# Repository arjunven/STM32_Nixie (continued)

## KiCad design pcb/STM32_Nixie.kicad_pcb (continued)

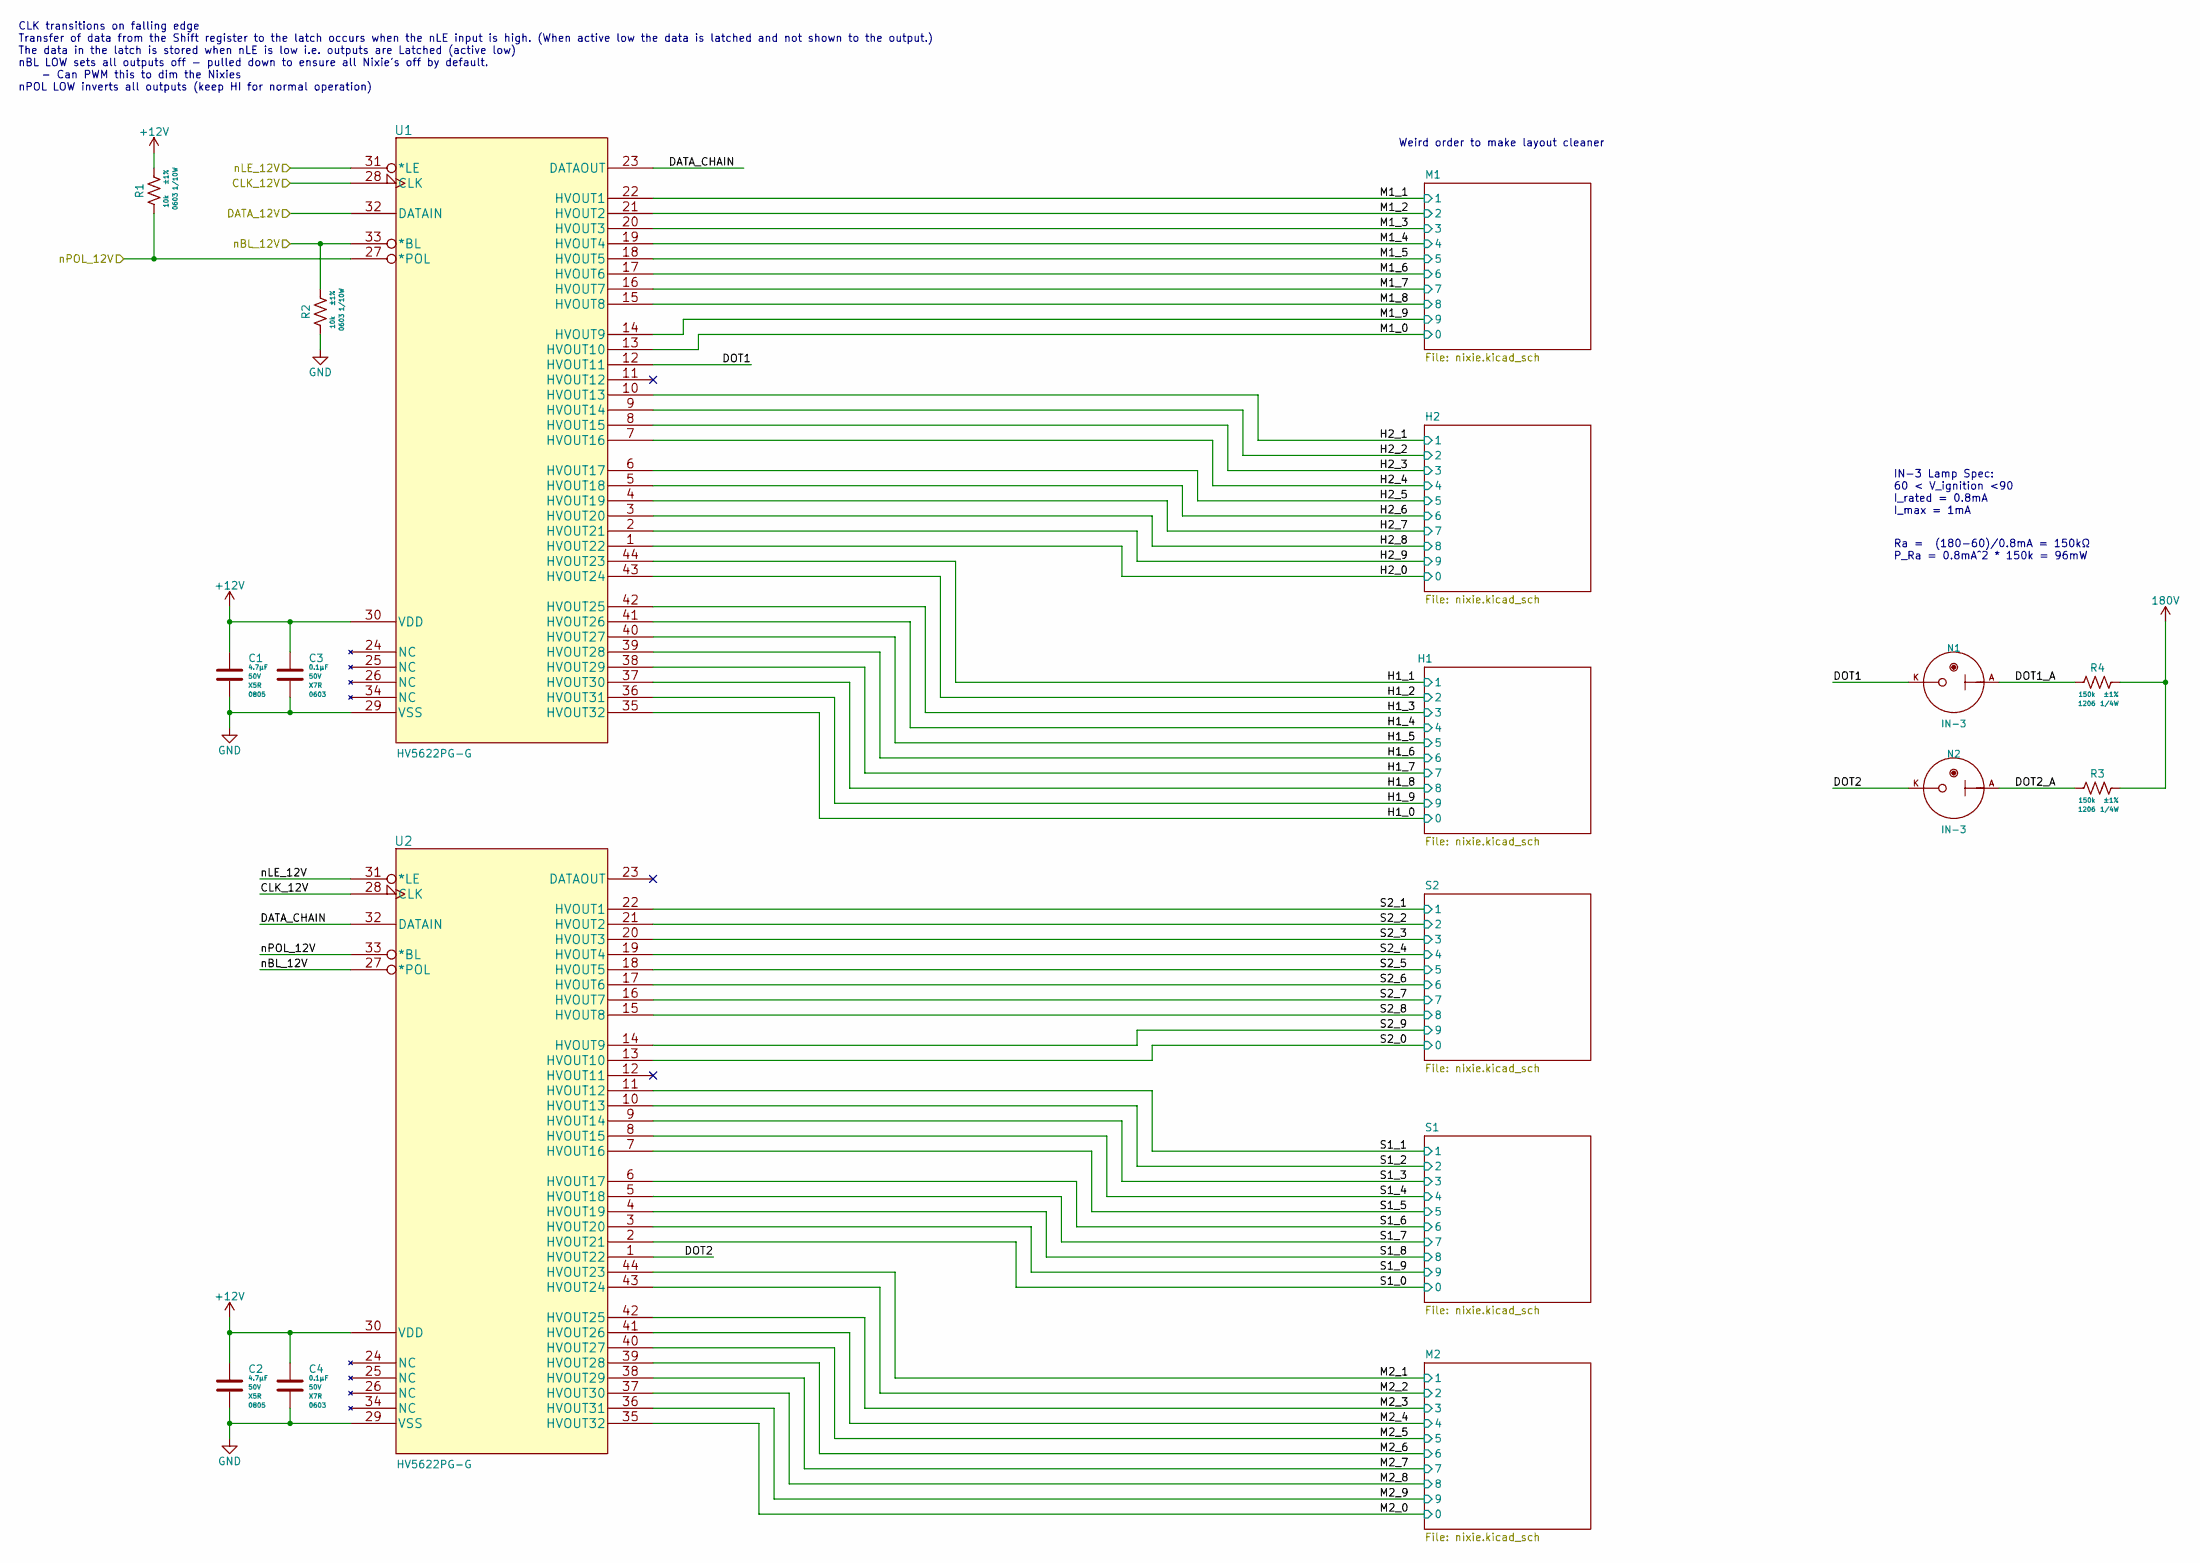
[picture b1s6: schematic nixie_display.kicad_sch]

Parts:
C1, C2: CAP_CER_4u7_50V_X5R_0805; C_0805_2012Metric; Voltage 50V; ManufacturerPN GRM21BR61H475KE51L
C3, C4: CAP_CER_0u1_50V_X7R_0603; C_0603_1608Metric; Voltage 50V; ManufacturerPN CL10B104KB8NNNC
N1, N2: IN-3
R1, R2: RES_10K_1P_1/10W_0603; R_0603_1608Metric; Tolerance ±1%; ManufacturerPN RC0603FR-0710KL
R3, R4: RES_150K_1P_1/4W_1206; R_1206_3216Metric; Tolerance ±1%; ManufacturerPN RC1206FR-07150KL
U1, U2: IC_SR_MC_HV5622PG-G; HV5622PG-G; ManufacturerPN HV5622PG-G

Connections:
180V: R3.1, R4.1; also elsewhere on the board
+12V: C1.1, C2.1, C3.1, C4.1, R1.1, U1.30 (VDD), U2.30 (VDD); also elsewhere on the board
/Nixie Display/DATA_CHAIN: U1.23 (DATAOUT), U2.32 (DATAIN)
/Nixie Display/DOT1: N1.K, U1.12 (HVOUT11)
/Nixie Display/DOT1_A: N1.A, R4.2
/Nixie Display/DOT2: N2.K, U2.1 (HVOUT22)
/Nixie Display/DOT2_A: N2.A, R3.2
/Nixie Display/H1_0: U1.35 (HVOUT32); also elsewhere on the board
/Nixie Display/H1_1: U1.44 (HVOUT23); also elsewhere on the board
/Nixie Display/H1_2: U1.43 (HVOUT24); also elsewhere on the board
/Nixie Display/H1_3: U1.42 (HVOUT25); also elsewhere on the board
/Nixie Display/H1_4: U1.41 (HVOUT26); also elsewhere on the board
/Nixie Display/H1_5: U1.40 (HVOUT27); also elsewhere on the board
/Nixie Display/H1_6: U1.39 (HVOUT28); also elsewhere on the board
/Nixie Display/H1_7: U1.38 (HVOUT29); also elsewhere on the board
/Nixie Display/H1_8: U1.37 (HVOUT30); also elsewhere on the board
/Nixie Display/H1_9: U1.36 (HVOUT31); also elsewhere on the board
/Nixie Display/H2_0: U1.1 (HVOUT22); also elsewhere on the board
/Nixie Display/H2_1: U1.10 (HVOUT13); also elsewhere on the board
/Nixie Display/H2_2: U1.9 (HVOUT14); also elsewhere on the board
/Nixie Display/H2_3: U1.8 (HVOUT15); also elsewhere on the board
/Nixie Display/H2_4: U1.7 (HVOUT16); also elsewhere on the board
/Nixie Display/H2_5: U1.6 (HVOUT17); also elsewhere on the board
/Nixie Display/H2_6: U1.5 (HVOUT18); also elsewhere on the board
/Nixie Display/H2_7: U1.4 (HVOUT19); also elsewhere on the board
/Nixie Display/H2_8: U1.3 (HVOUT20); also elsewhere on the board
/Nixie Display/H2_9: U1.2 (HVOUT21); also elsewhere on the board
/Nixie Display/M1_0: U1.13 (HVOUT10); also elsewhere on the board
/Nixie Display/M1_1: U1.22 (HVOUT1); also elsewhere on the board
/Nixie Display/M1_2: U1.21 (HVOUT2); also elsewhere on the board
/Nixie Display/M1_3: U1.20 (HVOUT3); also elsewhere on the board
/Nixie Display/M1_4: U1.19 (HVOUT4); also elsewhere on the board
/Nixie Display/M1_5: U1.18 (HVOUT5); also elsewhere on the board
/Nixie Display/M1_6: U1.17 (HVOUT6); also elsewhere on the board
/Nixie Display/M1_7: U1.16 (HVOUT7); also elsewhere on the board
/Nixie Display/M1_8: U1.15 (HVOUT8); also elsewhere on the board
/Nixie Display/M1_9: U1.14 (HVOUT9); also elsewhere on the board
/Nixie Display/M2_0: U2.35 (HVOUT32); also elsewhere on the board
/Nixie Display/M2_1: U2.44 (HVOUT23); also elsewhere on the board
/Nixie Display/M2_2: U2.43 (HVOUT24); also elsewhere on the board
/Nixie Display/M2_3: U2.42 (HVOUT25); also elsewhere on the board
/Nixie Display/M2_4: U2.41 (HVOUT26); also elsewhere on the board
/Nixie Display/M2_5: U2.40 (HVOUT27); also elsewhere on the board
/Nixie Display/M2_6: U2.39 (HVOUT28); also elsewhere on the board
/Nixie Display/M2_7: U2.38 (HVOUT29); also elsewhere on the board
/Nixie Display/M2_8: U2.37 (HVOUT30); also elsewhere on the board
/Nixie Display/M2_9: U2.36 (HVOUT31); also elsewhere on the board
/Nixie Display/S1_0: U2.2 (HVOUT21); also elsewhere on the board
/Nixie Display/S1_1: U2.11 (HVOUT12); also elsewhere on the board
/Nixie Display/S1_2: U2.10 (HVOUT13); also elsewhere on the board
/Nixie Display/S1_3: U2.9 (HVOUT14); also elsewhere on the board
/Nixie Display/S1_4: U2.8 (HVOUT15); also elsewhere on the board
/Nixie Display/S1_5: U2.7 (HVOUT16); also elsewhere on the board
/Nixie Display/S1_6: U2.6 (HVOUT17); also elsewhere on the board
/Nixie Display/S1_7: U2.5 (HVOUT18); also elsewhere on the board
/Nixie Display/S1_8: U2.4 (HVOUT19); also elsewhere on the board
/Nixie Display/S1_9: U2.3 (HVOUT20); also elsewhere on the board
/Nixie Display/S2_0: U2.13 (HVOUT10); also elsewhere on the board
/Nixie Display/S2_1: U2.22 (HVOUT1); also elsewhere on the board
/Nixie Display/S2_2: U2.21 (HVOUT2); also elsewhere on the board
/Nixie Display/S2_3: U2.20 (HVOUT3); also elsewhere on the board
/Nixie Display/S2_4: U2.19 (HVOUT4); also elsewhere on the board
/Nixie Display/S2_5: U2.18 (HVOUT5); also elsewhere on the board
/Nixie Display/S2_6: U2.17 (HVOUT6); also elsewhere on the board
/Nixie Display/S2_7: U2.16 (HVOUT7); also elsewhere on the board
/Nixie Display/S2_8: U2.15 (HVOUT8); also elsewhere on the board
/Nixie Display/S2_9: U2.14 (HVOUT9); also elsewhere on the board
/PWM_nBL_12V: R2.1, U1.33 (*BL), U2.27 (*POL); also elsewhere on the board
/SPI_PICO_12V: U1.32 (DATAIN); also elsewhere on the board
/SPI_SCK_12V: U1.28 (CLK), U2.28 (CLK); also elsewhere on the board
/SPI_nCS_nLE_12V: U1.31 (*LE), U2.31 (*LE); also elsewhere on the board
/nPOL_12V: R1.2, U1.27 (*POL), U2.33 (*BL); also elsewhere on the board
GND: C1.2, C2.2, C3.2, C4.2, R2.2, U1.29 (VSS), U2.29 (VSS); also elsewhere on the board

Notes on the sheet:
CLK transitions on falling edge Transfer of data from the Shift register to the latch occurs when the nLE input is high. (When active low the data is latched and not shown to the output.) The data in the latch is stored when nLE is low i.e. outputs are Latched (active low) nBL LOW sets all outputs 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
Ra = (180-60)/0.8mA = 150kΩ P_Ra = 0.8mA^2 * 150k = 96mW
Weird order to make layout cleaner
IN-3 Lamp Spec: 60 < V_ignition <90 I_rated = 0.8mA I_max = 1mA

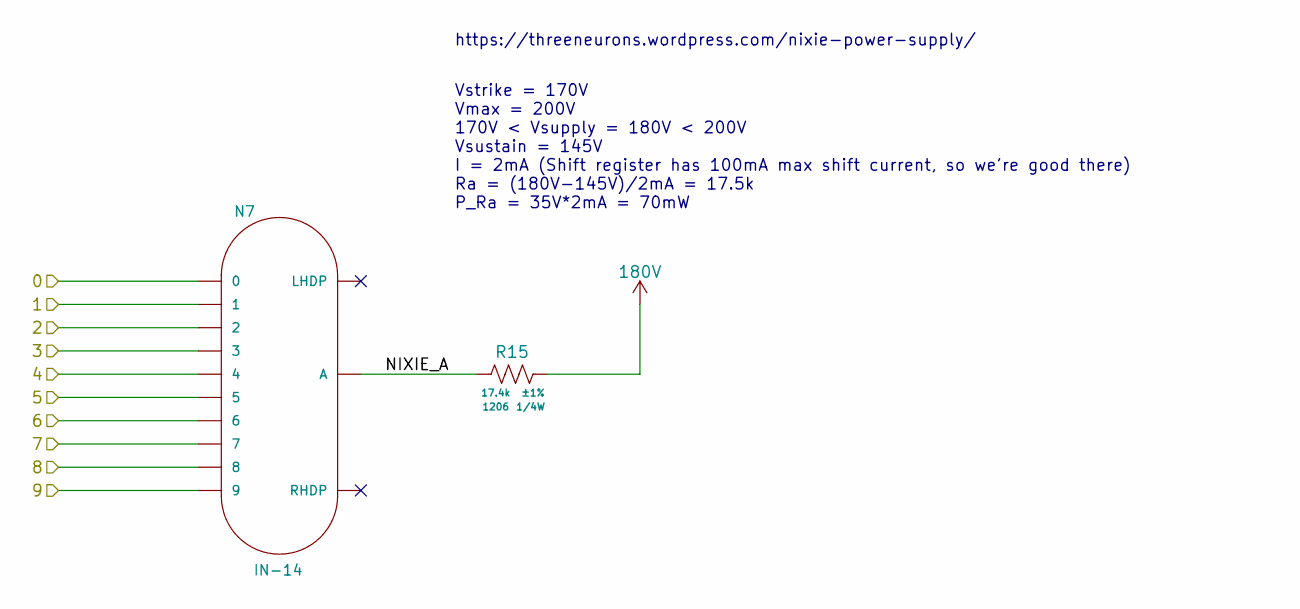
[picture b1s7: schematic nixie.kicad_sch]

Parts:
N7: IN-14
R15: RES_17K4_1P_1/4W_1206; R_1206_3216Metric; Tolerance ±1%; ManufacturerPN RC1206FR-0717K4L

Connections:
180V: R15.1; also elsewhere on the board
/Nixie Display/S1/NIXIE_A: N7.A, R15.2
/Nixie Display/S1_0: N7.0; also elsewhere on the board
/Nixie Display/S1_1: N7.1; also elsewhere on the board
/Nixie Display/S1_2: N7.2; also elsewhere on the board
/Nixie Display/S1_3: N7.3; also elsewhere on the board
/Nixie Display/S1_4: N7.4; also elsewhere on the board
/Nixie Display/S1_5: N7.5; also elsewhere on the board
/Nixie Display/S1_6: N7.6; also elsewhere on the board
/Nixie Display/S1_7: N7.7; also elsewhere on the board
/Nixie Display/S1_8: N7.8; also elsewhere on the board
/Nixie Display/S1_9: N7.9; also elsewhere on the board

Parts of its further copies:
N3, N4, N5, N6, N8: IN-14
R11, R12, R13, R14, R16: RES_17K4_1P_1/4W_1206; R_1206_3216Metric; Tolerance ±1%; ManufacturerPN RC1206FR-0717K4L

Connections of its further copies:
180V: R11.1, R12.1, R13.1, R14.1, R16.1; also elsewhere on the board
/Nixie Display/H1/NIXIE_A: N3.A, R11.2
/Nixie Display/H1_0: N3.0; also elsewhere on the board
/Nixie Display/H1_1: N3.1; also elsewhere on the board
/Nixie Display/H1_2: N3.2; also elsewhere on the board
/Nixie Display/H1_3: N3.3; also elsewhere on the board
/Nixie Display/H1_4: N3.4; also elsewhere on the board
/Nixie Display/H1_5: N3.5; also elsewhere on the board
/Nixie Display/H1_6: N3.6; also elsewhere on the board
/Nixie Display/H1_7: N3.7; also elsewhere on the board
/Nixie Display/H1_8: N3.8; also elsewhere on the board
/Nixie Display/H1_9: N3.9; also elsewhere on the board
/Nixie Display/H2/NIXIE_A: N4.A, R12.2
/Nixie Display/H2_0: N4.0; also elsewhere on the board
/Nixie Display/H2_1: N4.1; also elsewhere on the board
/Nixie Display/H2_2: N4.2; also elsewhere on the board
/Nixie Display/H2_3: N4.3; also elsewhere on the board
/Nixie Display/H2_4: N4.4; also elsewhere on the board
/Nixie Display/H2_5: N4.5; also elsewhere on the board
/Nixie Display/H2_6: N4.6; also elsewhere on the board
/Nixie Display/H2_7: N4.7; also elsewhere on the board
/Nixie Display/H2_8: N4.8; also elsewhere on the board
/Nixie Display/H2_9: N4.9; also elsewhere on the board
/Nixie Display/M1/NIXIE_A: N5.A, R13.2
/Nixie Display/M1_0: N5.0; also elsewhere on the board
/Nixie Display/M1_1: N5.1; also elsewhere on the board
/Nixie Display/M1_2: N5.2; also elsewhere on the board
/Nixie Display/M1_3: N5.3; also elsewhere on the board
/Nixie Display/M1_4: N5.4; also elsewhere on the board
/Nixie Display/M1_5: N5.5; also elsewhere on the board
/Nixie Display/M1_6: N5.6; also elsewhere on the board
/Nixie Display/M1_7: N5.7; also elsewhere on the board
/Nixie Display/M1_8: N5.8; also elsewhere on the board
/Nixie Display/M1_9: N5.9; also elsewhere on the board
/Nixie Display/M2/NIXIE_A: N6.A, R14.2
/Nixie Display/M2_0: N6.0; also elsewhere on the board
/Nixie Display/M2_1: N6.1; also elsewhere on the board
/Nixie Display/M2_2: N6.2; also elsewhere on the board
/Nixie Display/M2_3: N6.3; also elsewhere on the board
/Nixie Display/M2_4: N6.4; also elsewhere on the board
/Nixie Display/M2_5: N6.5; also elsewhere on the board
/Nixie Display/M2_6: N6.6; also elsewhere on the board
/Nixie Display/M2_7: N6.7; also elsewhere on the board
/Nixie Display/M2_8: N6.8; also elsewhere on the board
/Nixie Display/M2_9: N6.9; also elsewhere on the board
/Nixie Display/S2/NIXIE_A: N8.A, R16.2
/Nixie Display/S2_0: N8.0; also elsewhere on the board
/Nixie Display/S2_1: N8.1; also elsewhere on the board
/Nixie Display/S2_2: N8.2; also elsewhere on the board
/Nixie Display/S2_3: N8.3; also elsewhere on the board
/Nixie Display/S2_4: N8.4; also elsewhere on the board
/Nixie Display/S2_5: N8.5; also elsewhere on the board
/Nixie Display/S2_6: N8.6; also elsewhere on the board
/Nixie Display/S2_7: N8.7; also elsewhere on the board
/Nixie Display/S2_8: N8.8; also elsewhere on the board
/Nixie Display/S2_9: N8.9; also elsewhere on the board

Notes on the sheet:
Vstrike = 170V Vmax = 200V 170V < Vsupply = 180V < 200V Vsustain = 145V I = 2mA (Shift register has 100mA max shift current, so we're good there) Ra = (180V-145V)/2mA = 17.5k P_Ra = 35V*2mA = 70mW
https://threeneurons.wordpress.com/nixie-power-supply/

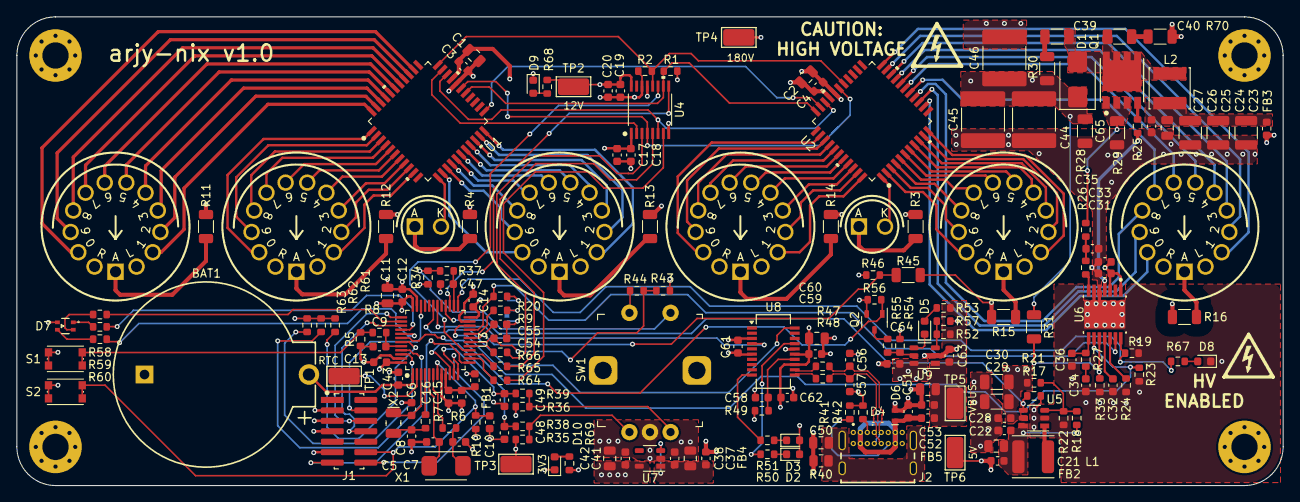
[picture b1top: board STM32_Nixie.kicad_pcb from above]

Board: 4 copper layers, 154.0 x 57.0 mm, 185 parts (1 on the bottom side), 172 nets.

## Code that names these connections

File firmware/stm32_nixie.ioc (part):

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Mcu.Name=STM32F100C(4-6)Tx
Mcu.Package=LQFP48
Mcu.UserName=STM32F100C4Tx
PA0-WKUP.GPIOParameters=GPIO_Label
PA0-WKUP.GPIO_Label=ENC_A
PA0-WKUP.Signal=S_TIM2_CH1_ETR
PA1.GPIOParameters=GPIO_Label
PA1.GPIO_Label=ENC_B
PA1.Signal=S_TIM2_CH2
PA10.GPIOParameters=GPIO_Label
PA10.GPIO_Label=UART1_BL_RX
PA10.Mode=Asynchronous
PA10.Signal=USART1_RX
PA13.Mode=Serial_Wire
PA13.Signal=SYS_JTMS-SWDIO
PA14.Mode=Serial_Wire
PA14.Signal=SYS_JTCK-SWCLK
PA15.GPIOParameters=GPIO_Label
PA15.GPIO_Label=LED_GREEN
PA15.Signal=GPIO_Output
PA2.GPIOParameters=GPIO_Label
PA2.GPIO_Label=UART2_VCP_TX
PA2.Mode=Asynchronous
PA2.Signal=USART2_TX
PA3.GPIOParameters=GPIO_Label
PA3.GPIO_Label=UART2_VCP_RX
PA3.Mode=Asynchronous
PA3.Signal=USART2_RX
PA4.GPIOParameters=GPIO_Label
PA4.GPIO_Label=SPI_nCS_nLE
PA4.Signal=GPIO_Output
PA5.GPIOParameters=GPIO_Label
PA5.GPIO_Label=SPI_SCK
PA5.Mode=TX_Only_Simplex_Unidirect_Master
PA5.Signal=SPI1_SCK
PA6.GPIOParameters=GPIO_Label
PA6.GPIO_Label=PWM_nBL
PA6.Signal=GPIO_Output
PA7.GPIOParameters=GPIO_Label
PA7.GPIO_Label=SPI_PICO
PA7.Mode=TX_Only_Simplex_Unidirect_Master
PA7.Signal=SPI1_MOSI
PA9.GPIOParameters=GPIO_Label
PA9.GPIO_Label=UART1_BL_TX
PA9.Mode=Asynchronous
PA9.Signal=USART1_TX
PB0.GPIOParameters=GPIO_Label
PB0.GPIO_Label=SENSE_12V
PB0.Signal=ADCx_IN8
PB1.GPIOParameters=GPIO_Label
PB1.GPIO_Label=SENSE_180V
PB1.Signal=ADCx_IN9
PB10.GPIOParameters=GPIO_Label
PB10.GPIO_Label=PG_180V
PB10.Signal=GPIO_Input
PB11.GPIOParameters=GPIO_Label
PB11.GPIO_Label=DITHOFF_180V
PB11.Signal=GPIO_Output
PB12.GPIOParameters=GPIO_Label
PB12.GPIO_Label=EN_180V
PB12.Signal=GPIO_Output
PB13.GPIOParameters=GPIO_Label
PB13.GPIO_Label=ENC_PB
PB13.Signal=GPIO_Input
PB14.GPIOParameters=GPIO_Label
PB14.GPIO_Label=nPOL
PB14.Signal=GPIO_Output
PB15.GPIOParameters=GPIO_Label
PB15.GPIO_Label=EN_12V
PB15.Signal=GPIO_Output
PB2.GPIOParameters=GPIO_Label
PB2.GPIO_Label=BOOT1
PB2.Signal=GPIO_Input
PB3.Signal=SYS_JTDO-TRACESWO
PB4.GPIOParameters=GPIO_Label
PB4.GPIO_Label=LED_RED
PB4.Signal=GPIO_Output
PB5.GPIOParameters=GPIO_Label
PB5.GPIO_Label=LED_BLUE
PB5.Signal=GPIO_Output
PB6.GPIOParameters=GPIO_Label
PB6.GPIO_Label=SET_ILIM
PB6.Signal=GPIO_Output
PB7.GPIOParameters=GPIO_PuPd,GPIO_Label
PB7.GPIO_Label=HW_REV2
PB7.GPIO_PuPd=GPIO_PULLUP
PB7.Signal=GPIO_Input
PB8.GPIOParameters=GPIO_PuPd,GPIO_Label
PB8.GPIO_Label=HW_REV1
PB8.GPIO_PuPd=GPIO_PULLUP
PB8.Signal=GPIO_Input
PB9.GPIOParameters=GPIO_PuPd,GPIO_Label
PB9.GPIO_Label=HW_REV0
PB9.GPIO_PuPd=GPIO_PULLUP
PB9.Signal=GPIO_Input
PC13-TAMPER-RTC.Mode=RTC OUT
PC13-TAMPER-RTC.Signal=RTC_OUT
PC14-OSC32_IN.Mode=LSE-External-Oscillator
PC14-OSC32_IN.Signal=RCC_OSC32_IN
PC15-OSC32_OUT.Mode=LSE-External-Oscillator
PC15-OSC32_OUT.Signal=RCC_OSC32_OUT
PD0-OSC_IN.Mode=HSE-External-Oscillator
PD0-OSC_IN.Signal=RCC_OSC_IN
PD1-OSC_OUT.Mode=HSE-External-Oscillator
PD1-OSC_OUT.Signal=RCC_OSC_OUT
RCC.SYSCLKFreq_VALUE=24000000
RCC.SYSCLKSource=RCC_SYSCLKSOURCE_PLLCLK
board=custom

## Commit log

2022-10-30 Backlink to CADLAB.io has been added.
2022-10-31 added mcu symbol
2022-11-04 Added MCU page and shift register.
2022-11-04 ignore the backups folder
2022-11-06 added a nixie symbol
2022-11-23 updated the nixie schematic
2022-11-24 wired up Nixie tubes
2022-11-26 Added level shifter and finished up HV Shift Register page
2022-11-27 Added USBC Connector to power page
2022-12-12 added some subfolders
2022-12-12 adding Eclipse standard .gitignore
2022-12-12 Started STM32CubeIDE project
2022-12-26 Added MCU bypassing
2022-12-28 Added LSE crystal and started configuring MCU Pinout"
2022-12-29 Added 8MHz Oscillator and mapped most of the MCU pins"
2022-12-29 Started mapping out MCU pins
2022-12-30 Added ferrite to ADC input, Coin-Cell, and STLINK conn.
2022-12-30 Added Boot mode selection
2023-01-02 Changed Boot0 switch to mom. pb, added rotary encoder, and nRST pb
2023-01-03 Added switch debouncing
2023-01-09 Added MCU pinouts for rotary encoder
2023-01-15 Added IN-3 dots, picked FTDI chip and 3.3V LDO
2023-01-29 added a sime of the 12V boost
2023-02-03 12V boost sim in a good place with calculated values
2023-02-04 Finished 12V boost circuit and updated sim to match
2023-02-04 Updated caps on 12V Boost, added caps for 3.3V LDO
2023-02-12 started some 180V sims
2024-03-04 Adding LM5156 spice files, but they dont work on LTspice :(
2024-03-13 Started adding 180V boost components
2024-04-08 Added FET, shunt, and shunt filter
2024-04-14 Added Diode and output caps to 180V Boost
2024-04-16 Added soft start cap
2024-04-21 Added most of the passives for the 180V supply
2024-05-02 Added bypass caps for Bias and Vcc connection to 12V
2024-05-11 Generic simulation models
2024-05-11 Playing around with effects of parasitics and snubbers
2024-05-11 Playing around with sims some more
2024-05-12 Ignore lt spice sim outputs more and autosave files from Kicad
2024-05-12 Added snubber DNP footprints and named nets on power page.
2024-05-13 Added 12V and 180V sense lines
2024-05-13 Updated pin mapping with power supply IOs
2024-05-16 Turns out CUBE ide doesnt want to generate code on a mac. But Im keeping the .ioc file for now for pin assignment.
2024-06-22 Updated ftdi page
2024-06-22 deleted the log files
2024-06-22 So apparently CubeIDE wants to work again for Mac -- shrug
2024-07-15 Added load switch to input to limit inrush
2024-07-15 Added load swtich current limit change FET and plumbed out signals to top level
2024-07-16 Added load switch fault LED and some notes on usb esd diodes
2024-08-05 Added ESD protection to 5V input, leds, hw rev pins, and test points.
2024-08-05 Updated pin mapping with hw rev pins and Ilim set for input load switch
2024-08-08 Fixed a bunch of footprints and added missing 3D models
2024-08-11 Ignore KiCad 8 lock files
2024-08-11 Started layout!! 180V boost mostly laid out
2024-08-12 Added 180V clearance rules. Updated 0805 footprints to 1206 for 180V nets.
2024-08-13 Started mcu placement
2024-08-18 Placement V1. Want to try and centre the board on the nixies vertically. Saving progress before trying out different placements.
2024-08-18 Liking this placement a lot better -- board is looking more symmetric north to south
2024-08-18 Placement wip
2024-08-22 Added note about mcu reset
2024-09-28 Routing progress! Maybe 30% done.
2024-09-29 50% done routing. Power pour progress!
2024-09-29 Making progress on nixie tube signal routing
2024-09-29 Updated uart names to include peripheral number
2024-09-30 Reshuffled nixie schematic to ease with routing. Need to fix the other 3 digits next.
2024-10-06 Reshuffled Nixie page some more to make routing cleaner
2024-10-06 All nets routed!! (I think)
2024-10-07 Ref Designators cleaned up. Started DRC squashing
2024-10-10 Added teardrops and removed unused pad shapes.
2024-10-10 Final cleanup and some more GND via stitching.
2024-10-11 Some silk additions
2024-10-12 Feeling ready to generate gerbers!
2024-10-12 Some minor tweaks and generated gerbers
2024-10-16 Generated outputs for built round 2
2024-10-19 Adding stm32 / cpp specific ignores
2024-10-20 Updating .gitignore with some tweaks
2024-10-20 pushing final save
2024-10-20 Set up project with CMake in Vscode
2024-10-20 Renamed to cpp
2024-10-20 Started driver for hv5622
2024-10-20 Modified structure to have seperate header and source file for periphs and made our own main_app.cpp so that CubeMX doesnt clobber it everytime it autogenerates.
2024-10-20 Stop tracking build.ninja
2024-10-20 Ignoring generated ninja files
2024-10-20 Adding CMakePresets.json
2024-10-20 Updating Cmake file to include new main_app.cpp. Also fixing RAM syntax error in linker script caused by the latest version of CubeMX *sigh*
2024-10-21 updated hv5622 driver to use SPI and GPIO periphs
2024-10-28 Adding clang format
2024-10-28 Updating SPI data size to 8bit
2024-10-28 Driver started
2024-11-02 Added some wrapper functions for the blanking and polarity pins
2024-11-03 Set SPI periph in mode 1. CPOL = 0 and CPHA = 1 to clock data out on falling edges.
2024-11-04 Realized I got my tube naming backwards. Updated schematic with correct naming annotations
2024-11-04 Started nixie_display driver that abstracts the shift register writes to direct digits on the tubes.
2024-11-13 Added remainder of the DIGIT_MAP
2024-11-13 Started implementing nixie_display set_digit driver
2024-11-17 Finished set_digit and added clear implementation
2024-11-18 Added some vscode specific config files for STM32 dev in vscode
2024-11-18 Adding launch.json
2024-11-18 Updated to keep original config
2024-11-18 Some board bringup scratch
2024-11-20 WIP on display driver
2024-11-21 MVP for nixi_display driver
2024-11-25 Going through bring-up -- trying to get SPI driver working with level shifter
2024-11-25 Ignore .DS_Store at all levels
2024-11-25 Add step export of PCB
2024-11-29 Updated HV5622 blanking pin to a GPIO for now until the dimming gets implemented later
2024-11-29 Updated c++ header files to be .hh
2024-12-01 Switched to gpio chip select -- and hv5622 driver is working well!
2024-12-03 Bringup code in main_app - time to clean it up
2024-12-03 Restructured to have seperate App folder
2024-12-03 Starting a system control module to handle power up sequencing and init
2024-12-04 Finished power up sequence
2024-12-06 Ignore .cache folder from clangd.
2024-12-06 Mucking with cmake files to get clangd working right
2024-12-06 Added .clangd settings
2024-12-06 Added gpio_init
2024-12-07 Some final tweaks to files to make it work best with clangd.
2024-12-08 Some edits to work more nicely
2024-12-08 Messing with includes to appease clangd
2024-12-08 Added ability to have a blank tube when setting display
2024-12-09 Added time_lord class and added a blank digits function to the display
2024-12-09 It freakin tells time!!
2024-12-09 Project save
2024-12-09 added hal manual and organized
2024-12-11 Added virtual com port based UART debug messages
2024-12-15 Added basic user input class to track push button encoder states!
2024-12-16 Added button press duration detection
2024-12-16 Starting menu system to enbale setting time
2024-12-16 Added menu
2024-12-16 Started defining header for menu
2024-12-19 Started fleshing out states for menu
2024-12-21 Turns out getting a blinking digit requires a lot of re jiggering
2024-12-21 Extended blinking framework to be any number of digits
2024-12-22 Adding a time utils file to handle time utilities used across the menu and time_lord
2024-12-22 Added time_utils
2024-12-22 First draft of menu to set the time
2024-12-22 Semi functional menu system. Encoder input is not so smoot though. Still janky
2024-12-23 Fixed encoder update bug!
2024-12-23 Added a slot machine animation feature
2024-12-23 Updated int in for loop to uint8_t
2024-12-23 Start clock from 0
2024-12-23 Added slot machine animation on hour roll over and on boot
2024-12-23 Added slot machine animation on time set too :)
2025-01-04 Configured RTC backup register to allow time preservation after power off
2025-07-28 Create README.md
    document some of the project
2025-07-28 Added schematics pdf
2025-07-28 Update README.md with schematic
